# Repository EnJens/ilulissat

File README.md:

# Ilulissat
Ilulissat is a wireless environment sensor board, intended to run as low power as possible.

It consists of:
* [EFR32MG21](https://www.silabs.com/wireless/zigbee/efr32mg21-series-2-socs) Cortex M33 wireless chip
* [HDC2080](http://www.ti.com/product/HDC2080) Environment Sensor (Temperature and Relative Humidity)

The wireless chip supports both Bluetooth, Zigbee and OpenThread.

The first revision of the software will be written for Bluetooth Low energy using
a standard profile, e.g Temperature and Humidity, hopefully allowing it to use some standard
app off playstore/apple appstore.

## Images

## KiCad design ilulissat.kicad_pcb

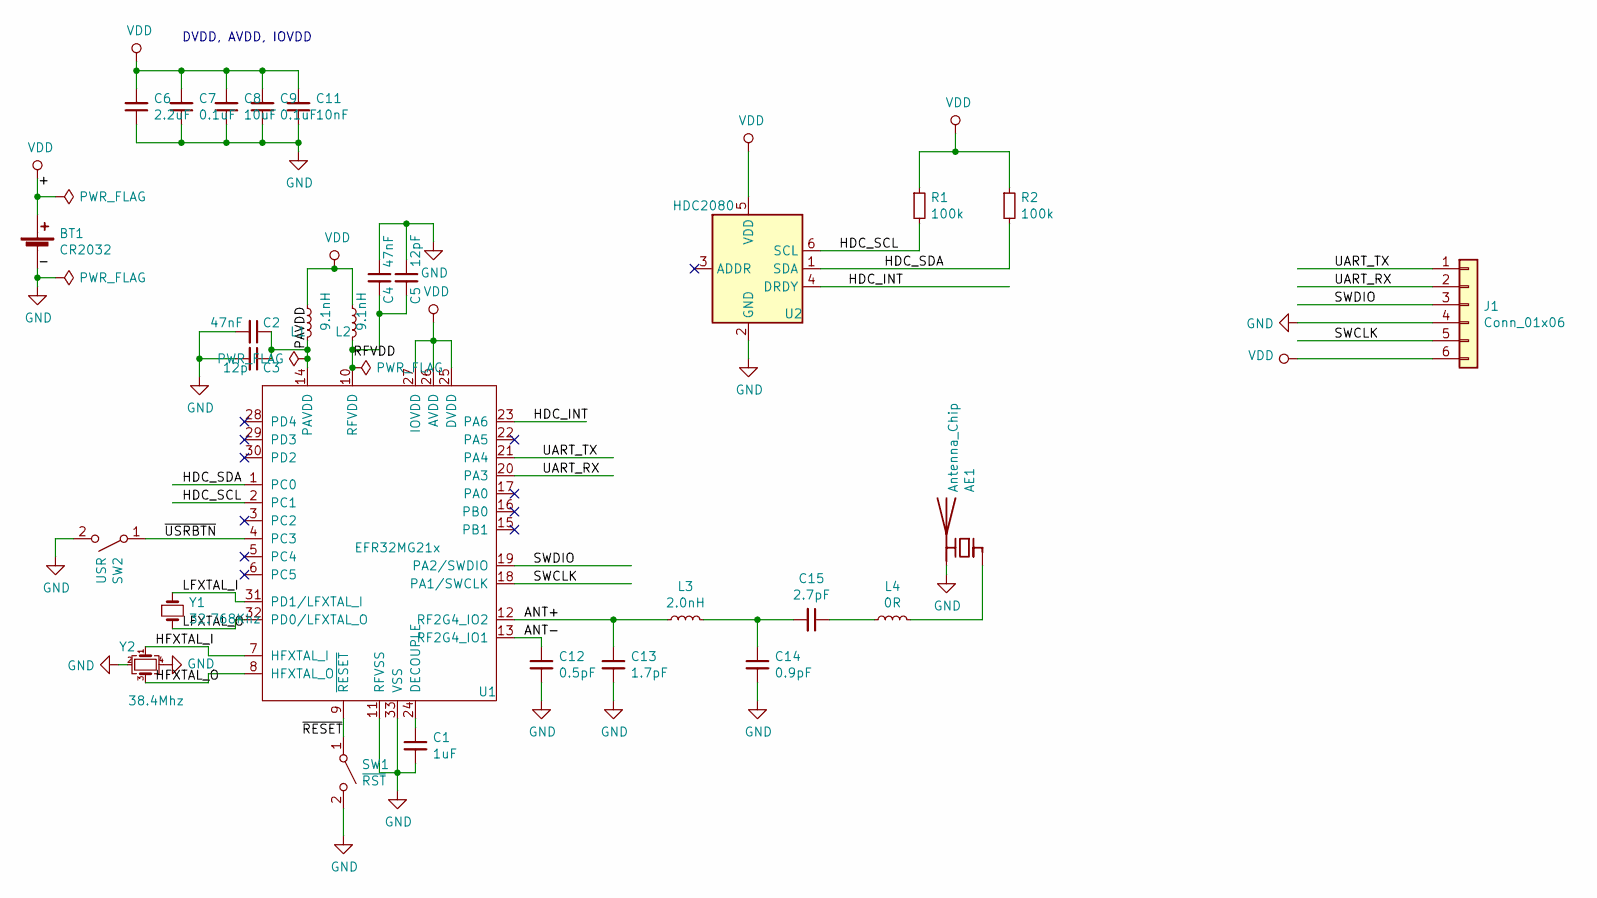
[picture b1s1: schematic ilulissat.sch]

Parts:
AE1: Antenna_Chip; Antenna_Johanson_2450AT42E0100; LCSC C127620
BT1: CR2032; BatteryHolder_Linx_BAT-HLD-001-THM
C1: 1uF; C_0402_1005Metric
C2, C4: 47nF; C_0402_1005Metric
C3: 12p; C_0402_1005Metric
C5: 12pF; C_0402_1005Metric
C6: 2.2uF; C_0402_1005Metric
C7, C9: 0.1uF; C_0402_1005Metric
C8: 10uF; C_0402_1005Metric
C11: 10nF; C_0402_1005Metric
C12: 0.5pF; C_0402_1005Metric
C13: 1.7pF; C_0402_1005Metric
C14: 0.9pF; C_0402_1005Metric
C15: 2.7pF; C_0402_1005Metric
J1: Conn_01x06; PinHeader_1x06_P1.27mm_Vertical
L1, L2: 9.1nH; L_0402_1005Metric; LCSC C281011
L3: 2.0nH; L_0402_1005Metric
L4: 0R; L_0402_1005Metric
R1, R2: 100k; R_0402_1005Metric
SW1: ~RST~; SW_SPST_B3U-1000P
SW2: USR; SW_SPST_B3U-1000P
U1: EFR32MG21x; QFN-32-1EP_4x4mm_P0.4mm_EP2.65x2.65mm
U2: HDC2080; Texas_PWSON-N6
Y1: 32.768Khz; Crystal_SMD_2012-2Pin_2.0x1.2mm; Mouser 520-.327-12.5-12R-T
Y2: 38.4Mhz; Crystal_SMD_3225-4Pin_3.2x2.5mm; Mouser 520-384-10-33B-CKYT

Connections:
/ANT+: C13.1, L3.1, U1.12 (RF2G4_IO2)
/ANT-: C12.1, U1.13 (RF2G4_IO1)
/HDC_INT: U1.23 (PA6), U2.4 (DRDY)
/HDC_SCL: R1.2, U1.2 (PC1), U2.6 (SCL)
/HDC_SDA: R2.2, U1.1 (PC0), U2.1 (SDA)
/HFXTAL_I: U1.7 (HFXTAL_I), Y2.1
/HFXTAL_O: U1.8 (HFXTAL_O), Y2.3
/LFXTAL_I: U1.31 (PD1/LFXTAL_I), Y1.1
/LFXTAL_O: U1.32 (PD0/LFXTAL_O), Y1.2
/PAVDD: C2.1, C3.1, L1.2, U1.14 (PAVDD)
/RFVDD: C4.2, C5.2, L2.2, U1.10 (RFVDD)
/SWCLK: J1.5, U1.18 (PA1/SWCLK)
/SWDIO: J1.3, U1.19 (PA2/SWDIO)
/UART_RX: J1.2, U1.20 (PA3)
/UART_TX: J1.1, U1.21 (PA4)
/USRLED: U1.3 (PC2); also elsewhere on the board
/~RESET~: SW1.1 (A), U1.9 (~RESET)
/~USRBTN~: SW2.1 (A), U1.4 (PC3)
GND: AE1.2 (PCB_Trace), BT1.2 (-), C1.2, C2.2, C3.2, C4.1, C5.1, C6.1, C7.1, C8.1, C9.1, C11.1, C12.2, C13.2, C14.2, J1.4, SW1.2 (B), SW2.2 (B), U1.11 (RFVSS), U1.33 (VSS), U2.2 (GND), Y2.2, Y2.4; also elsewhere on the board
unnamed: AE1.1 (FEED), L4.2
unnamed: C1.1, U1.24 (DECOUPLE)
unnamed: C14.1, C15.2, L3.2
unnamed: C15.1, L4.1
VDD: BT1.1 (+), C6.2, C7.2, C8.2, C9.2, C11.2, J1.6, L1.1, L2.1, R1.1, R2.1, U1.25 (DVDD), U1.26 (AVDD), U1.27 (IOVDD), U2.5 (VDD)

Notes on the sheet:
DVDD, AVDD, IOVDD

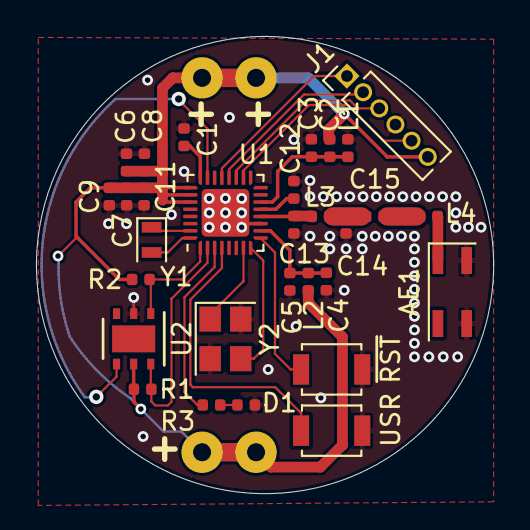
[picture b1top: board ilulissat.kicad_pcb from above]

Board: 2 copper layers, 25.4 x 25.4 mm, 31 parts (1 on the bottom side), 25 nets.

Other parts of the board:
D1: RED; LED_0402_1005Metric
R3: 360R; R_0402_1005Metric

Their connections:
/USRLED: R3.1; also elsewhere on the board
GND: D1.1; also elsewhere on the board
unnamed: D1.2, R3.2

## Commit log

2020-01-19 Initial project
2020-01-19 Add initial EFR32MG21 symbol
2020-01-19 More work
2020-01-20 Start adding footprints, fill in remaining components
2020-01-21 More parts
2020-02-06 WIP WIP
2020-02-09 Routing complete, needs cleanup
2020-02-09 Don't track gerbers
2020-02-09 Round a track
2020-02-09 Add a user button
2020-02-09 Add schematic PDF
2020-02-09 Fun tests
2020-02-09 Finished?
2020-02-09 Align some text
2020-02-09 Update schematic PDF
2020-02-09 trivial readme
2020-02-10 Add UART
2020-02-10 Add LED
2020-02-10 Make DRC unhappy for less risk of shorts
2020-02-16 Rev1
2020-02-16 Rev 1 gerbers
